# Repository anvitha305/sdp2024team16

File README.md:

# sdp2024team16 - Evaluation of the Inertial Measurement Units (IMUs) we Wanted to Use

Our team has run an evaluation on all the available IMU models at both makerspaces to determine which ones would be the best for our purposes.

## BMI160+BMM150 Shuttleboard
Prior to our determination that we wanted onboard processing capability as a feature for the IMUs, we selected this IMU due to its resolution being on the same order as the BNO055 (a Zero-Offset error of +- 1-2 degrees per second with a 250 degrees per second system), and its power consumption being on the order of 100s of microamps as opposed to milliamps, since we were cognizant of the implications of needing multiple sensors on one bow that were heavily power-consuming. However, this shuttleboard is obsolete, which speaks to the fact that there is improved technology in the field for the same purposes, and there is currently a lack of support from Bosch (the manufacturer of these IMUs) and to prototype with these boards we would need to write our own processing algorithm for handling the data received from this sensor, which would add an extensive amount of effort to a section of the project which is not a priority as it is not the novel component of the project.

## LSM9DS1 
After determining our issues with the shuttleboard, we decided to pivot to analyzing two variants of IMUs with onboard processing capabilities. The LSM9DS1 was one of two available options with this criteria. We evaluated with a compass and the archery range that an accuracy of ~1-2 degrees per second in a 250 degrees per second system was the specification that worked best in our case with maintaining aim accuracy. We decided that triangulating IMUs on varying positions of the bow would facilitate improving accuracy because it would enable us to get multiple perspectives on the direction of the arrow and improve the aim of the user.  The information about the LSM9DS1’s accuracy does not provide a small range of expected accuracy, stating  <30dps with a 250dps system according to the datasheet, which lead us to believe that the accuracy of the LSM9DS1 would not likely fit our specifications that we outlined in Section D. Further, the typical power draw was 4.3mA for the LSM9DS1.

## BNO055
In conclusion of our initial analysis of the Inertial Measurement Units for this project, we have chosen the BNO055, as its accuracy is on the order of the Bosch BMI160 and BMM150 shuttleboard while having onboard processing capabilities, both of which are on the order we analyzed to be acceptable for our purposes. We found that its low power mode provided a typical draw of 2.7mA, compromising the sensor reading rate as a result, and its typical draw on average was 3.1mA, which is considerably higher than the shuttleboard but understandable due to the convenience that it affords us.

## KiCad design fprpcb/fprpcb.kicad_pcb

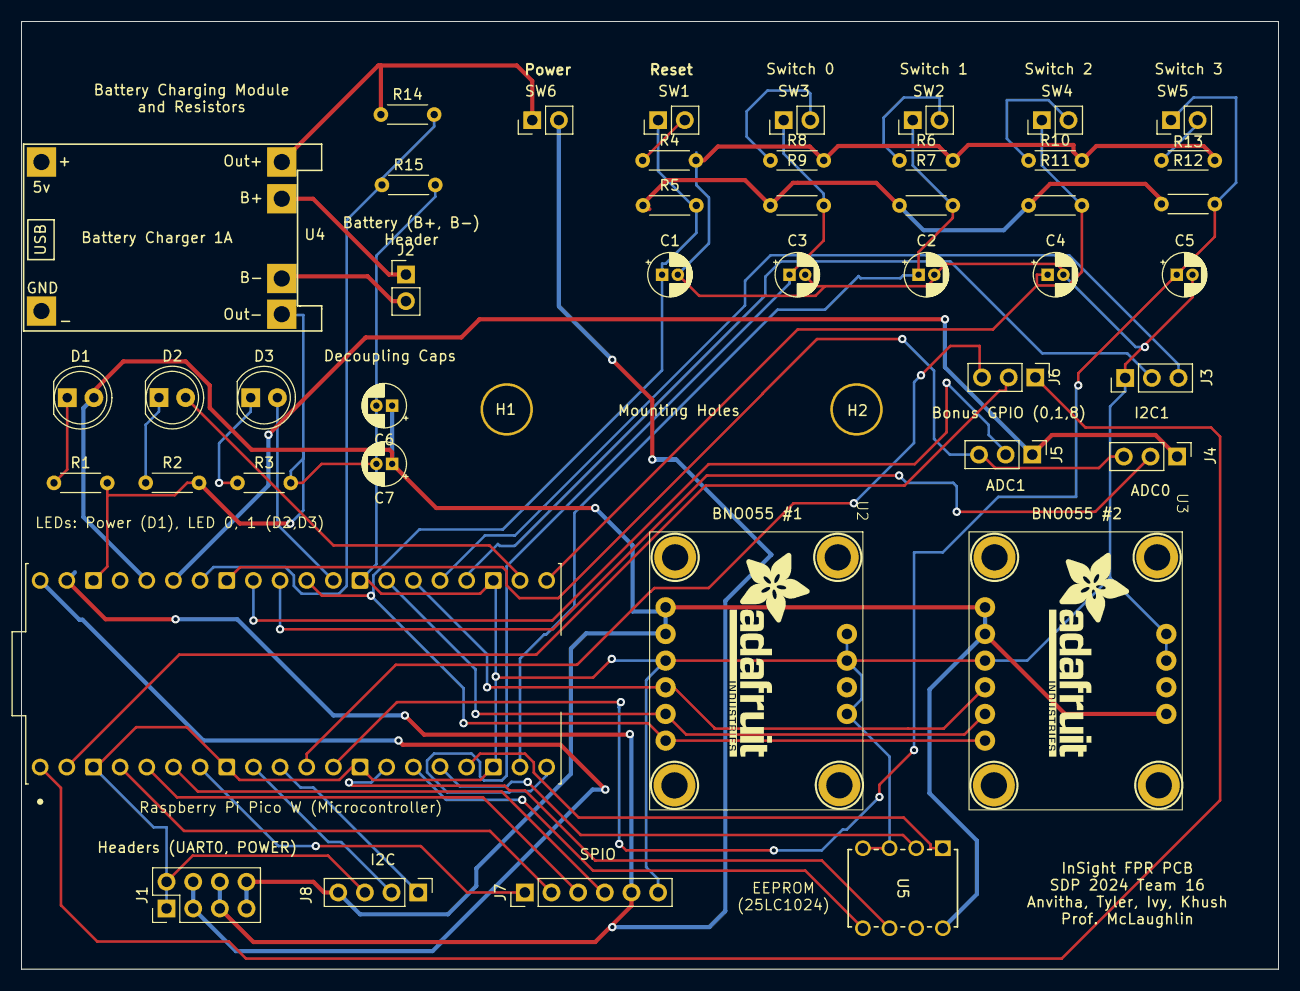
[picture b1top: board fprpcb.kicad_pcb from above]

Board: 2 copper layers, 119.8 x 90.3 mm, 46 parts (0 on the bottom side), 45 nets.

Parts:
C1, C2, C3, C4, C5: 100nF; CP_Radial_D4.0mm_P1.50mm
C6: 100n; CP_Radial_D4.0mm_P1.50mm
C7: 1u; CP_Radial_D4.0mm_P1.50mm
D1, D2, D3: LED; LED_D5.0mm
H1, H2: MountingHole; MountingHole_4.5mm
J1: Conn_02x04_Odd_Even; PinHeader_2x04_P2.54mm_Vertical
J2: Conn_01x02; PinHeader_1x02_P2.54mm_Vertical
J3, J4, J5, J6: Conn_01x03; PinHeader_1x03_P2.54mm_Vertical
J7: Conn_01x06; PinHeader_1x06_P2.54mm_Vertical
J8: Conn_01x04; PinHeader_1x04_P2.54mm_Vertical
R1, R2, R3: 330; R_Axial_DIN0204_L3.6mm_D1.6mm_P5.08mm_Horizontal
R4, R6, R8, R10, R13: 100; R_Axial_DIN0204_L3.6mm_D1.6mm_P5.08mm_Horizontal
R5, R7, R9, R11, R12: 10k; R_Axial_DIN0204_L3.6mm_D1.6mm_P5.08mm_Horizontal
R14: 3.3k; R_Axial_DIN0204_L3.6mm_D1.6mm_P5.08mm_Horizontal
R15: 1k; R_Axial_DIN0204_L3.6mm_D1.6mm_P5.08mm_Horizontal
SW1, SW2, SW3, SW4, SW5, SW6: Conn_01x02_Pin; PinHeader_1x02_P2.54mm_Vertical
U1: SC0918; MODULE_SC0918
U2, U3: BNO055_Breakout
U4: TP4056-18650
U5: 25LC1024-I/P; PDIP8_300MC_MCH

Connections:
+3.3V: C6.1, C7.1, D1.2 (A), J1.7, J1.8, J8.4, U1.36 (3V3_OUT), U2.1 (Vin), U2.2 (3Vo), U3.1 (Vin), U3.2 (3Vo), U3.10 (ADR), U5.8 (VCC)
+3V3: R5.1, R7.1, R9.1, R11.1, R12.1
/B+: J2.1, U4.2 (B+)
/B-: J2.2, U4.3 (B-)
/GP0_UART0_TX: J6.1, U1.1 (GP0)
/GP1_UART0_RX: J6.2, U1.2 (GP1)
/GP6_INT: J8.2, U1.9 (GP6)
/GP7_AD0: J8.1, U1.10 (GP7)
/GP8_UART1_TX: J6.3, U1.11 (GP8)
/GP26_ADC0: J4.2, U1.31 (GP26)
/GP27_ADC1: J5.2, U1.32 (GP27)
/GP28_ADC2: R14.2, R15.1, U1.34 (GP28)
/I2C0_SCL: U1.27 (GP21), U2.5 (SCL), U3.5 (SCL)
/I2C0_SDA: U1.26 (GP20), U2.4 (SDA), U3.4 (SDA)
/I2C1_SCL: J3.3, U1.25 (GP19)
/I2C1_SDA: J3.2, U1.24 (GP18)
/LED0: D2.2 (A), U1.22 (GP17)
/LED1: D3.2 (A), U1.29 (GP22)
/RST: C1.1, R5.2, SW1.1, U1.30 (~RUN), U2.6 (RST), U3.6 (RST)
/SPI0_CS: J7.1, U1.7 (GP5)
/SPI0_MISO: J7.4, U1.6 (GP4)
/SPI0_MOSI: J7.3, U1.5 (GP3)
/SPI0_SCK: J7.2, U1.4 (GP2)
/SPI1_CS: U1.17 (GP13), U5.1 (*CS)
/SPI1_MISO: U1.16 (GP12), U5.2 (SO)
/SPI1_MOSI: U1.15 (GP11), U5.5 (SI)
/SPI1_SCK: U1.14 (GP10), U5.6 (SCK)
/SW0: C2.1, R7.2, SW2.1, U1.19 (GP14)
/SW1: C3.1, R9.2, SW3.1, U1.20 (GP15)
/SW2: C4.1, R11.2, SW4.1, U1.21 (GP16)
/SW3: C5.1, R12.2, SW5.1, U1.12 (GP9)
GND: C1.2, C2.2, C3.2, C4.2, C5.2, C6.2, C7.2, J1.1, J1.2, J3.1, J7.6, J8.3, R1.2, R2.2, R3.2, R4.2, R6.2, R8.2, R10.2, R13.2, R15.2, U1.3 (GND), U1.8 (GND), U1.13 (GND), U1.18 (GND), U1.23 (GND), U1.28 (GND), U1.38 (GND), U2.3 (GND), U2.7 (PS0), U2.8 (PS1), U2.10 (ADR), U3.3 (GND), U3.7 (PS0), U3.8 (PS1), U4.4 (OUT-), U5.3 (*WP), U5.4 (VSS)
GNDA: J4.3, J5.3, U1.33 (AGND)
unnamed: D1.1 (K), R1.1
unnamed: D2.1 (K), R2.1
unnamed: D3.1 (K), R3.1
unnamed: R4.1, SW1.2
unnamed: R6.1, SW2.2
unnamed: R8.1, SW3.2
unnamed: R10.1, SW4.2
unnamed: R13.1, SW5.2
Out+: R14.1, SW6.1, U4.1 (OUT+)
VBUS: J1.3, J1.4, U1.40 (VBUS)
VDDA: J4.1, J5.1, U1.35 (ADC_VREF)
VSYS: J1.5, J1.6, J7.5, SW6.2, U1.39 (VSYS)

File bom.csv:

Collated Components for CDRPCB:,,,
,,,
Item,Qty,Reference(s),Value
1,5,"C1, C2, C3, C4, C5",100nF
2,3,"D1, D2, D3",LED
3,1,J1,Conn_02x04_Odd_Even
4,4,"J2, J3, J4, J5",Conn_01x03
5,1,J7,Conn_01x06
6,1,J8,Conn_01x04
7,3,"R1, R2, R3",330
8,5,"R4, R6, R8, R10, R13",100
9,5,"R5, R7, R9, R11, R12",10k
10,1,R14,3.3k
11,1,R15,1k
12,5,"SW1, SW2, SW3, SW4, SW5",Conn_01x02_Pin
13,1,U1,SC0918
14,2,"U2, U3",~
15,1,U4,~
16,1,U5,25LC1024-I/P

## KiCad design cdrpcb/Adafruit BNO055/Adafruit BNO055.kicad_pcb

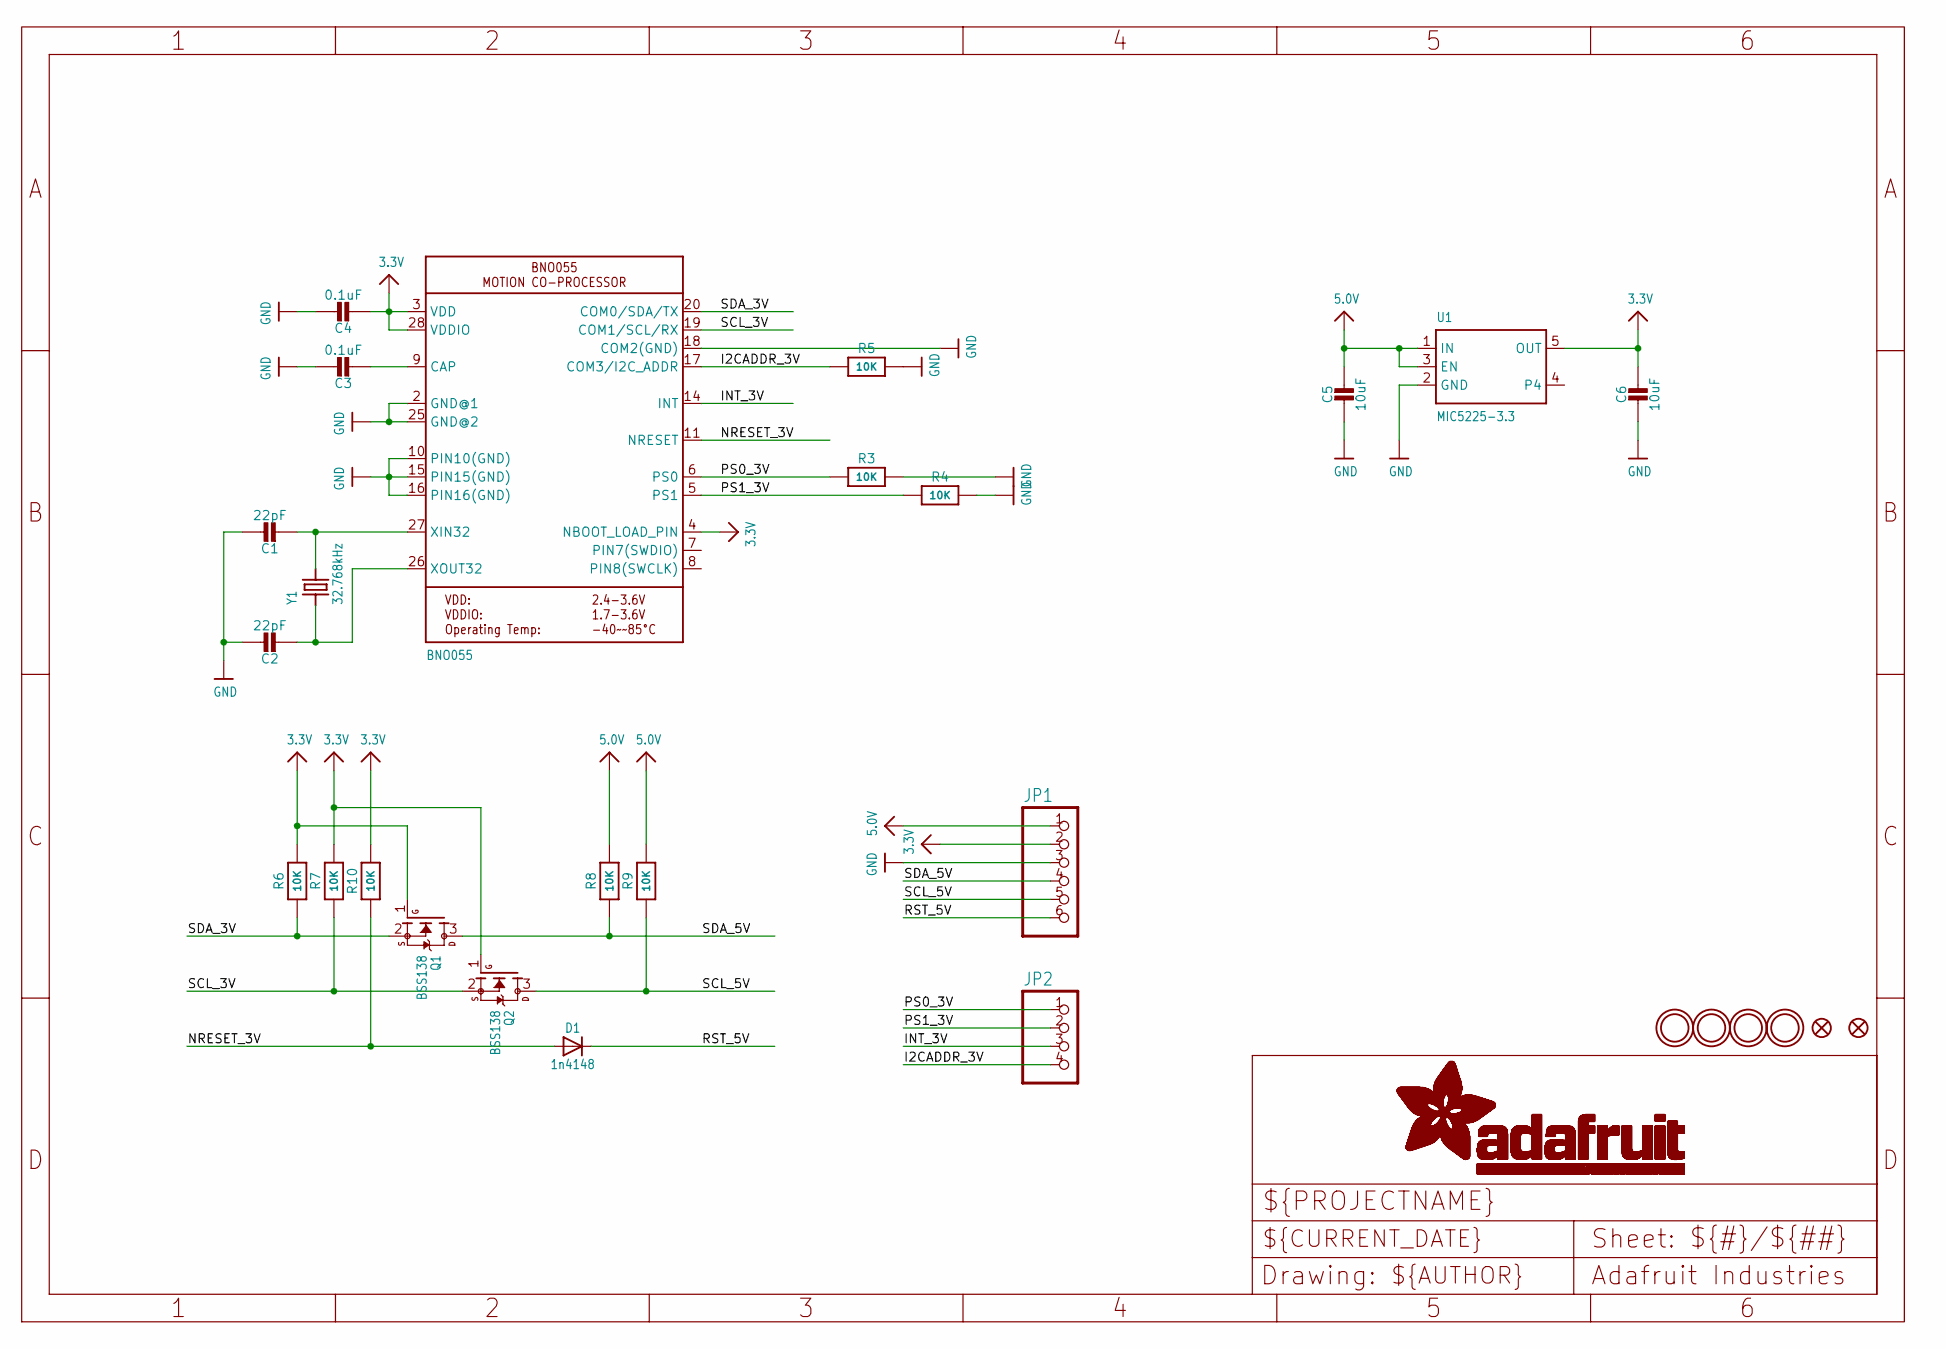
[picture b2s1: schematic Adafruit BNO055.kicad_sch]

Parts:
C1, C2: 22pF; 0805-NO
C3: 0.1uF; 0805-NO
C4: 0.1uF; 0805_10MGAP
C5: 10uF; 0805-NO
C6: 10uF; 0805_10MGAP
D1: 1n4148; SOD-323
FID1, FID2: FIDUCIAL""; FIDUCIAL_1MM
JP1: HEADER-1X676MIL; 1X06_ROUND_76
JP2: HEADER-1X476MIL; 1X04_ROUND_76
Q1, Q2: BSS138; SOT23-WIDE
R3, R4, R5, R6, R7, R10: 10K; 0805-NO
R8, R9: 10K; _0805MP
U1: MIC5225-3.3; SOT23-5
U$2: BNO055
U$29, U$30, U$31, U$32: MOUNTINGHOLE2.5_THICK; MOUNTINGHOLE_2.5_PLATED_THICK
Y1: 32.768kHz; CRYSTAL_8X3.8

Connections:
3.3V: C4.2, C6.1, JP1.2, Q1.1 (G), Q2.1 (G), R6.2, R7.2, R10.2, U1.5 (OUT), U$2.3 (VDD), U$2.4 (NBOOT_LOAD_PIN), U$2.28 (VDDIO)
5.0V: C5.1, JP1.1, R8.2, R9.2, U1.1 (IN), U1.3 (EN)
GND: C1.1, C2.1, C3.1, C4.1, C5.2, C6.2, JP1.3, R3.2, R4.2, R5.2, U1.2 (GND), U$2.2 (GND@1), U$2.10 (PIN10(GND)), U$2.15 (PIN15(GND)), U$2.16 (PIN16(GND)), U$2.18 (COM2(GND)), U$2.25 (GND@2)
I2CADDR_3V: JP2.4, R5.1, U$2.17 (COM3/I2C_ADDR)
INT_3V: JP2.3, U$2.14 (INT)
unnamed: C1.2, U$2.27 (XIN32), Y1.P$4 (2)
unnamed: C2.2, U$2.26 (XOUT32), Y1.P$1 (1)
unnamed: C3.2, U$2.9 (CAP)
NRESET_3V: D1.A, R10.1, U$2.11 (NRESET)
PS0_3V: JP2.1, R3.1, U$2.6 (PS0)
PS1_3V: JP2.2, R4.1, U$2.5 (PS1)
RST_5V: D1.C, JP1.6
SCL_3V: Q2.2 (S), R7.1, U$2.19 (COM1/SCL/RX)
SCL_5V: JP1.5, Q2.3 (D), R9.1
SDA_3V: Q1.2 (S), R6.1, U$2.20 (COM0/SDA/TX)
SDA_5V: JP1.4, Q1.3 (D), R8.1

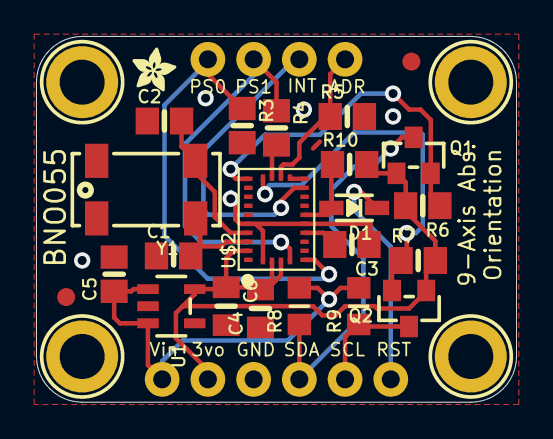
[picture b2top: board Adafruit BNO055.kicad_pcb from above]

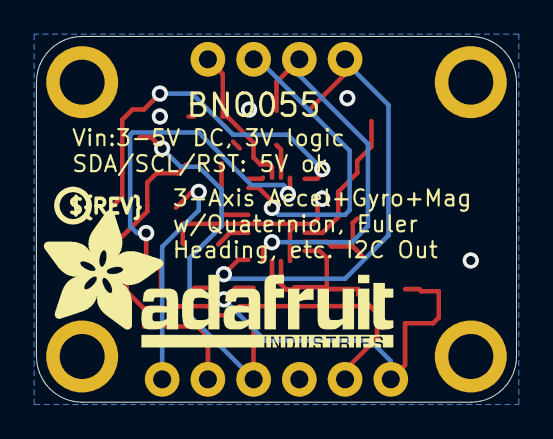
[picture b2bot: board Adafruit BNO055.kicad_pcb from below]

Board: 2 copper layers, 26.7 x 20.3 mm, 31 parts (2 on the bottom side), 16 nets.

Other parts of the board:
U$3: PCBFEAT-REV-040
U$28: ADAFRUIT_TEXT_20MM
U$33: ADAFRUIT_2.5MM

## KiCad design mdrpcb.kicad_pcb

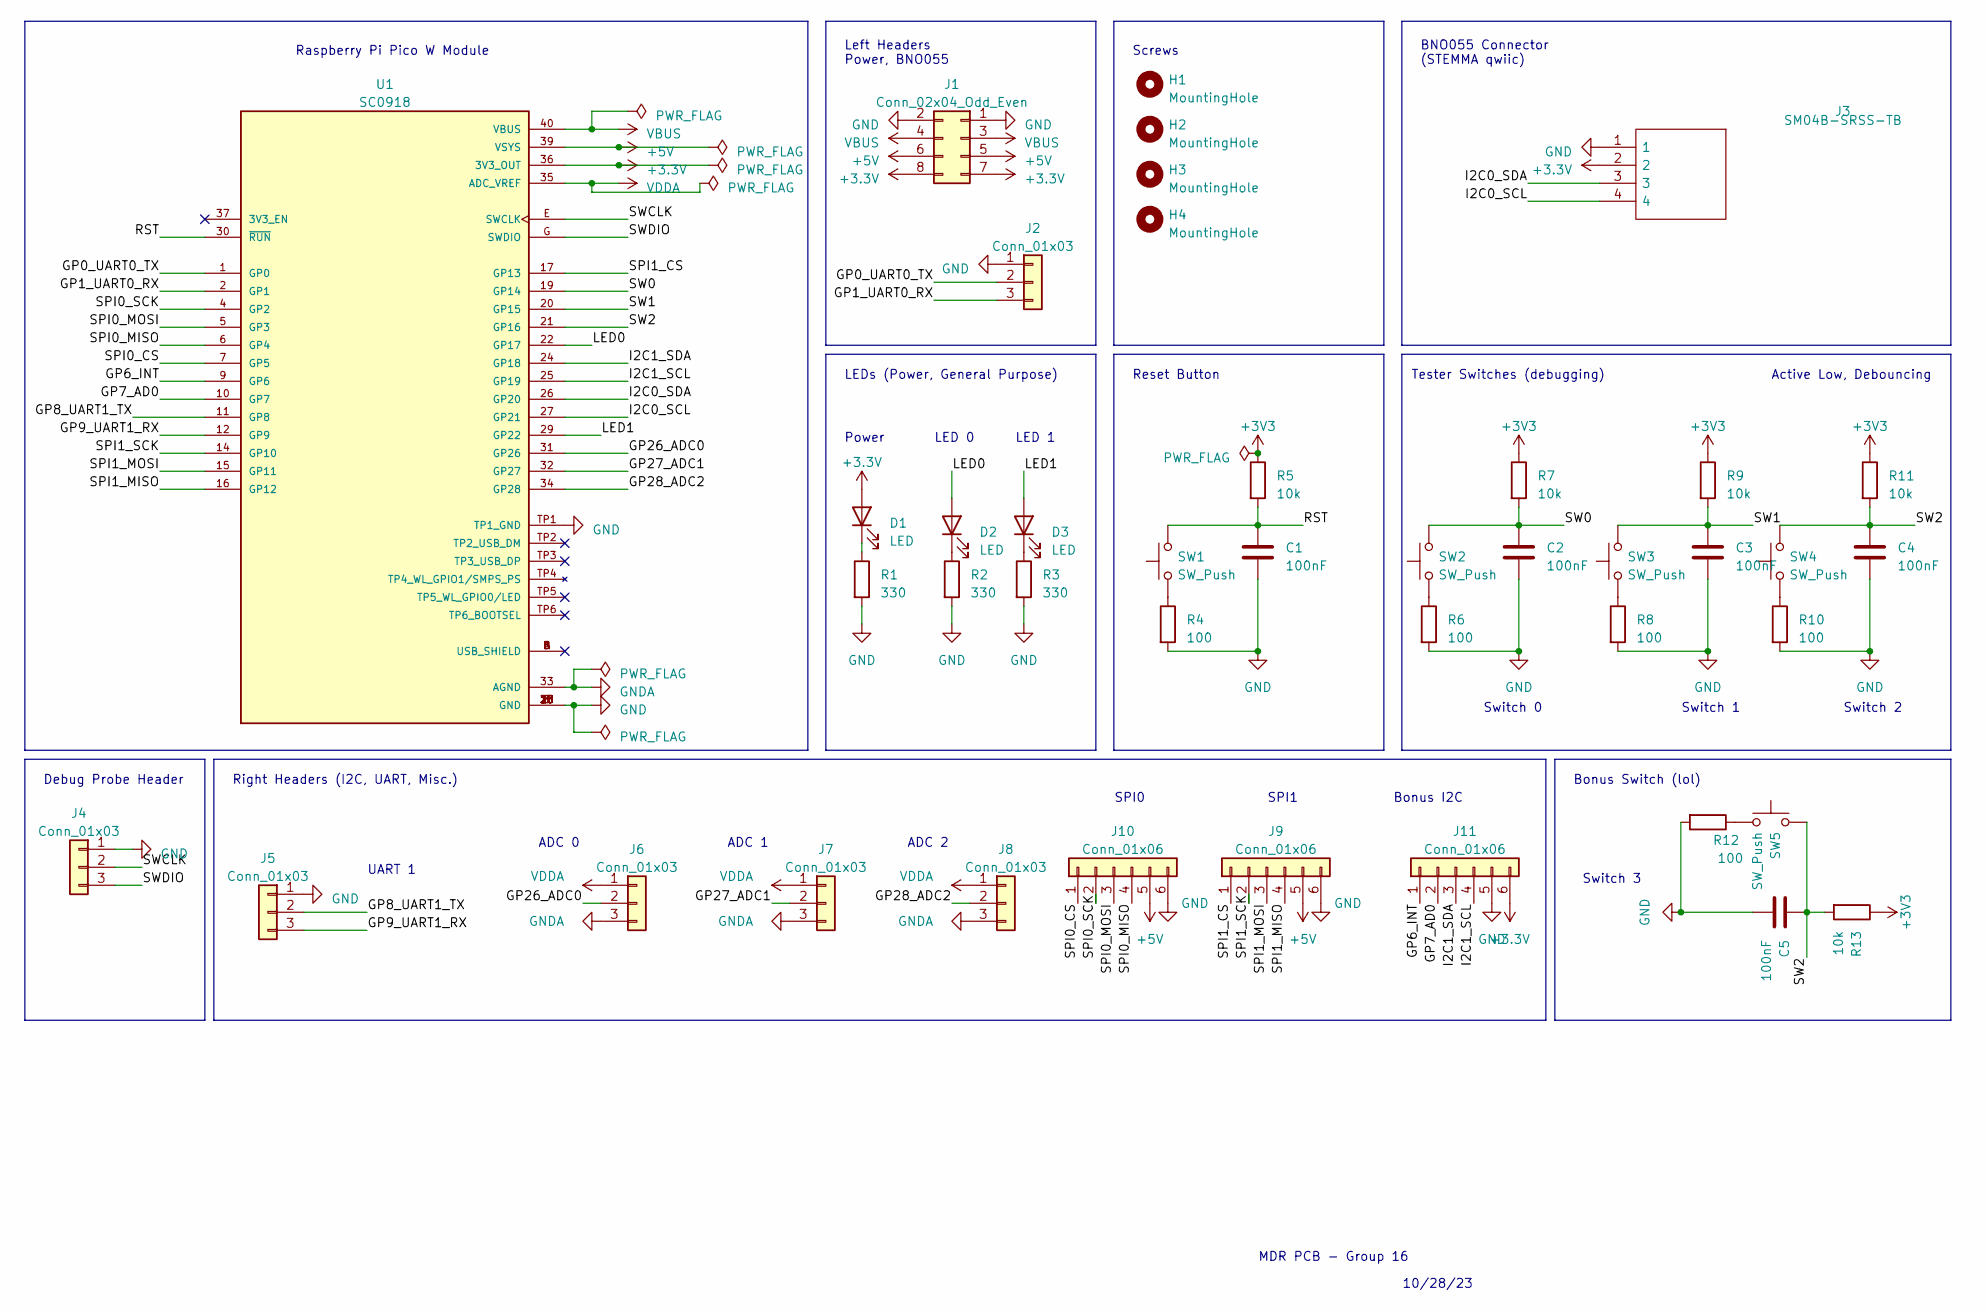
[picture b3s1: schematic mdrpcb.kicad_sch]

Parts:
C1, C2, C3, C4, C5: 100nF; CP_Radial_D4.0mm_P1.50mm
D1, D2, D3: LED; LED_D5.0mm
H1, H2, H3, H4: MountingHole; MountingHole_3.2mm_M3_ISO7380
J1: Conn_02x04_Odd_Even; PinHeader_2x04_P1.00mm_Vertical
J2, J4, J5, J6, J7, J8: Conn_01x03; PinHeader_1x03_P1.00mm_Vertical
J3: SM04B-SRSS-TB; SAMTEC-SMH-105-02-X-D; Manufacturer_Part_Number SM04B-SRSS-TB
J9, J10, J11: Conn_01x06; PinHeader_1x06_P1.00mm_Vertical
R1, R2, R3: 330; R_Axial_DIN0204_L3.6mm_D1.6mm_P1.90mm_Vertical
R4, R6, R8, R10, R12: 100; R_Axial_DIN0204_L3.6mm_D1.6mm_P1.90mm_Vertical
R5, R7, R9, R11, R13: 10k; R_Axial_DIN0204_L3.6mm_D1.6mm_P1.90mm_Vertical
SW1, SW2, SW3, SW4, SW5: SW_Push; SW_PUSH_6mm
U1: SC0918; MODULE_SC0918; PARTREV 2.1

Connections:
+3.3V: D1.2 (A), J1.7, J1.8, J3.2, J11.6, U1.36 (3V3_OUT)
+3V3: R5.1, R7.1, R9.1, R11.1, R13.1
+5V: J1.5, J1.6, J9.5, J10.5, U1.39 (VSYS)
/GP0_UART0_TX: J2.2, U1.1 (GP0)
/GP1_UART0_RX: J2.3, U1.2 (GP1)
/GP6_INT: J11.1, U1.9 (GP6)
/GP7_AD0: J11.2, U1.10 (GP7)
/GP8_UART1_TX: J5.2, U1.11 (GP8)
/GP9_UART1_RX: J5.3, U1.12 (GP9)
/GP26_ADC0: J6.2, U1.31 (GP26)
/GP27_ADC1: J7.2, U1.32 (GP27)
/GP28_ADC2: J8.2, U1.34 (GP28)
/I2C0_SCL: J3.4, U1.27 (GP21)
/I2C0_SDA: J3.3, U1.26 (GP20)
/I2C1_SCL: J11.4, U1.25 (GP19)
/I2C1_SDA: J11.3, U1.24 (GP18)
/LED0: D2.2 (A), U1.22 (GP17)
/LED1: D3.2 (A), U1.29 (GP22)
/RST: C1.1, R5.2, SW1.2, U1.30 (~RUN)
/SPI0_CS: J10.1, U1.7 (GP5)
/SPI0_MISO: J10.4, U1.6 (GP4)
/SPI0_MOSI: J10.3, U1.5 (GP3)
/SPI0_SCK: J10.2, U1.4 (GP2)
/SPI1_CS: J9.1, U1.17 (GP13)
/SPI1_MISO: J9.4, U1.16 (GP12)
/SPI1_MOSI: J9.3, U1.15 (GP11)
/SPI1_SCK: J9.2, U1.14 (GP10)
/SW0: C2.1, R7.2, SW2.2, U1.19 (GP14)
/SW1: C3.1, R9.2, SW3.2, U1.20 (GP15)
/SW2: C4.1, C5.1, R11.2, R13.2, SW4.2, SW5.2, U1.21 (GP16)
/SWCLK: J4.2, U1.E (SWCLK)
/SWDIO: J4.3, U1.G (SWDIO)
GND: C1.2, C2.2, C3.2, C4.2, C5.2, J1.1, J1.2, J2.1, J3.1, J4.1, J5.1, J9.6, J10.6, J11.5, R1.2, R2.2, R3.2, R4.2, R6.2, R8.2, R10.2, R12.2, U1.3 (GND), U1.8 (GND), U1.13 (GND), U1.18 (GND), U1.23 (GND), U1.28 (GND), U1.38 (GND), U1.F (GND), U1.TP1 (TP1_GND)
GNDA: J6.3, J7.3, J8.3, U1.33 (AGND)
unnamed: D1.1 (K), R1.1
unnamed: D2.1 (K), R2.1
unnamed: D3.1 (K), R3.1
unnamed: R4.1, SW1.1
unnamed: R6.1, SW2.1
unnamed: R8.1, SW3.1
unnamed: R10.1, SW4.1
unnamed: R12.1, SW5.1
VBUS: J1.3, J1.4, U1.40 (VBUS)
VDDA: J6.1, J7.1, J8.1, U1.35 (ADC_VREF)

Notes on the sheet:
LED 1
Screws
MDR PCB - Group 16
ADC 1
10/28/23
Debug Probe Header
BNO055 Connector (STEMMA qwiic)
Raspberry Pi Pico W Module
Tester Switches (debugging)
SPI1
Right Headers (I2C, UART, Misc.)
LED 0
UART 1
Left Headers Power, BNO055
Bonus Switch (lol)
Reset Button
SPI0
ADC 2
Power
Active Low, Debouncing
Switch 1
Switch 0
Switch 3
Switch 2
LEDs (Power, General Purpose)
Bonus I2C
ADC 0

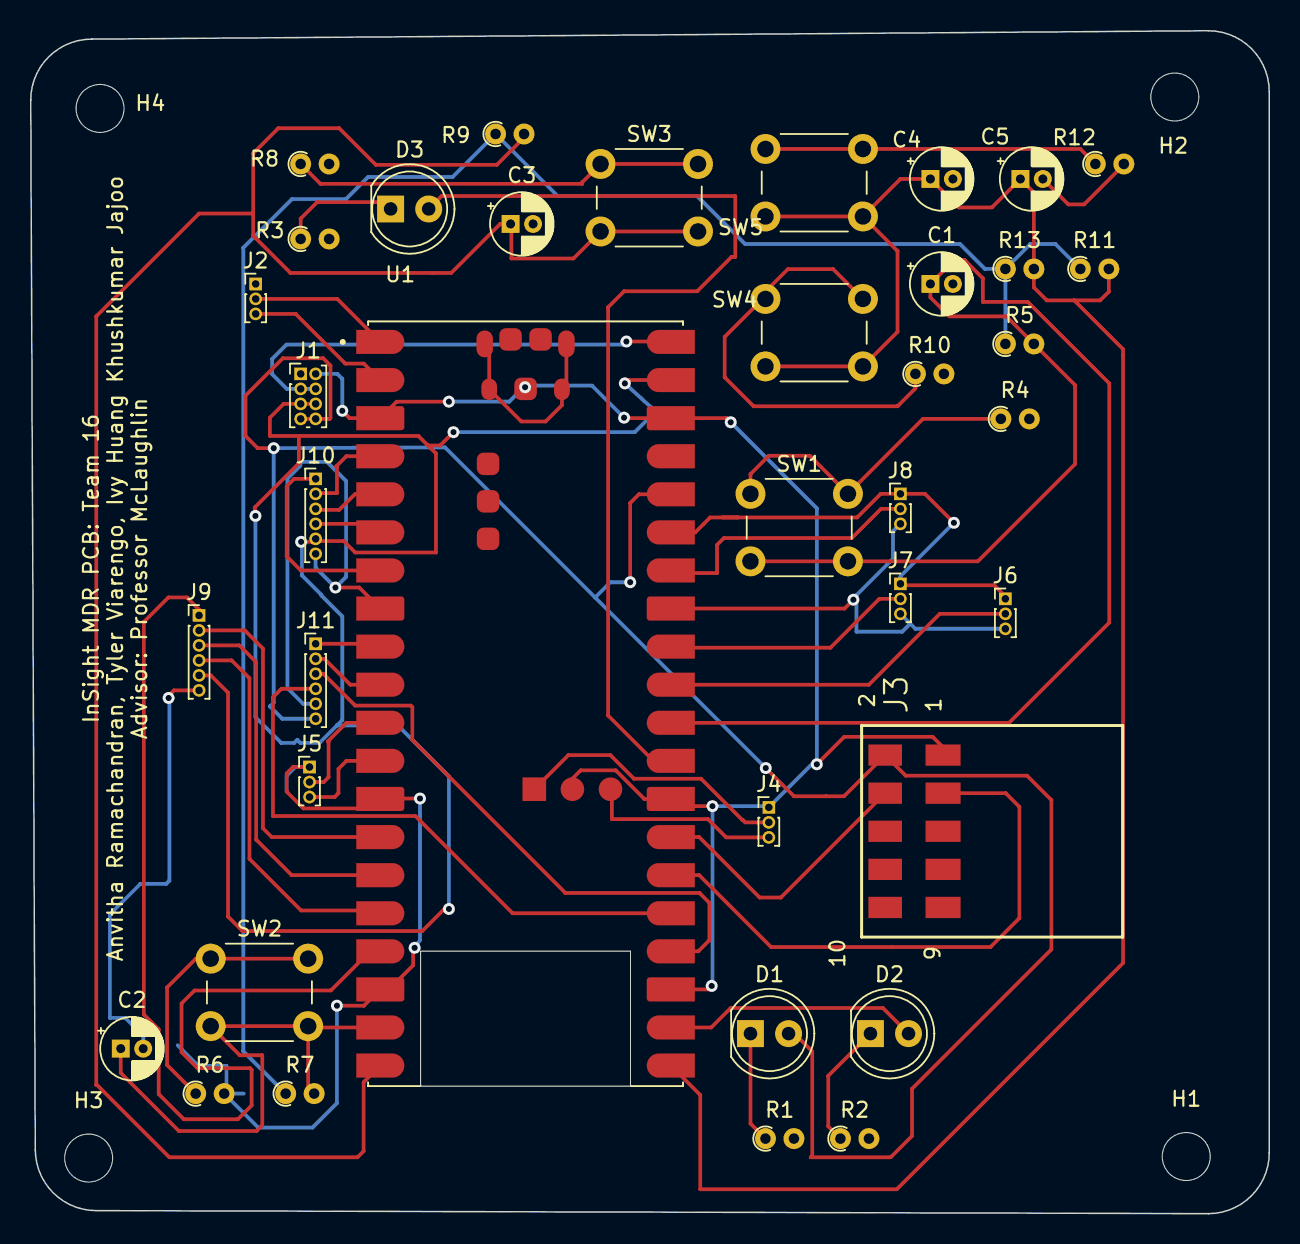
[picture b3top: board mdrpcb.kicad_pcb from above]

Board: 2 copper layers, 82.6 x 78.9 mm, 42 parts (0 on the bottom side), 44 nets.

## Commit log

2023-09-28 imu test for the BMI160
2023-10-04 adding to the readme
2023-10-21 IMU info
2023-11-06 completed repo
2023-11-13 Added numerical solver script
2023-11-13 Integrated ballistics script into simulator
2023-11-14 Switched to 4th order diffeq calculations
2023-11-15 Display Interval =/= Calculation Interval
2023-11-17 Some optimizations
2023-11-29 Create DisplayButtons
2023-11-29 Create DisplayTest
2023-11-29 Create PerspectiveProjection
2023-12-03 better and newer imu code :))
2023-12-03 Update PerspectiveProjection
2023-12-03 Update sim.py
    Integrating the simulator with the arduino stuff :)
2024-02-21 Added cdrpcb1
2024-02-21 Added latest display code
2024-02-24 cdrpcb2
2024-02-27 update cdrpcb
    bno055 footprints
2024-02-28 cdrpcb3
    Started routing
2024-03-01 cdrpcb4
    Routed the PCB
2024-03-02 cdrpcb5
    centered the mounting holes
2024-03-02 Re-routed with increased pwr/gnd thickness and overall clearance
2024-03-03 add labels, fix charging circuit traces
2024-03-03 widened traces, fixed charging circuit (for real)
2024-03-04 fixing mounting hole distancing and spacing issues and also adding in custom 5.0mm footprint for holes in KiCad
2024-03-04 cdrpcb Final
    added the gerber files
2024-03-06 Added ino of integrated code, needs testing
2024-03-08 Update MainDisplayIntegrated.ino
    change SPI chip select pin for the eeprom
2024-03-08 Update MainDisplayIntegrated.ino
    changed the pins to resolve EEPROM + display conflict
2024-03-10 Battery code
2024-03-12 PCB iteration with download, drill and appropriately named schematic
2024-03-12 Working RP2040 Integrated Code
2024-03-12 Bill of Materials for assembly of PCB
2024-03-28 FPR PCB Iter. 1
    Fixed stuff from CDR report
2024-03-29 updated fprpcb
2024-03-29 fixed power switch issue where ghost components were showing up on the board
2024-03-29 fprpcb (again and fr this time 💀)
2024-03-29 fprpcb
2024-03-29 SDP teams FPRPCB
2024-03-30 Revert "fprpcb"
    This reverts commit a24959e1a84143555ed98c59d3b6709d6d6878c6.
2024-03-31 fixed the errors described by Tyler on 3/29 morning
2024-03-31 update repo with true PCB that has all the fixed ones because the old one only updated the schematic
    💀💀💀💀💀💀💀
2024-03-31 Clean up gross track ends
    little itty bitty track ends are the death of me 💀
2024-03-31 verifying all traces to be correct size and clearance
2024-03-31 Updated FPRPCB based on 3/30 feedback
2024-04-10 fprpcb.csv
    bill of materials for the fprpcb
2024-04-22 Updated with Working Code from Apr 21 (IMUs currently spewing incorrect data)
2024-04-23 Update MainDisplayIntegrated.ino
    Updated for acceleration due to grav 💀
2024-04-24 Almost done :)
2024-04-25 Updated UI
